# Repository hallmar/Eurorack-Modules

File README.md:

# Eurorack-Modules
Hardware: cc-by-sa-3.0

Software: CC BY-SA 4.0

All of the code in this repository is for Arduino.

But if you want to sell or do something with the software or hardware then it'd be nice to include my name and link to my Github somewhere :)

This is a general repository for any and all eurorack modules that i have designed.
I also put DIY stuff here that I made PCB's from some other designers schematic. For example the MFOS PCB.

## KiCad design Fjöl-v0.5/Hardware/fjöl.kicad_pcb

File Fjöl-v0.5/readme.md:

# Fjöl 4-Voice Midi synth, THIS IS A DEPRECATED PROJECT AND I'M ONLY KEEPING IT FOR ARCHIVING PURPOSES

Current hardware uses a high quality DAC(PCM5100) with 16bit/44.1kHz quality.

It has MIDI IN and MIDI OUT/THRU. It uses the Arturia Standard for DIN to stereo jack, so type B midi.
You can find adapters in almost every synthstore now. 

## Designed With

* KiCAD
* Arduino IDE
* Audio System Design Tool for Teensy Audio Library

## Versioning
* 1.0 - [Hardware] Original PCB
* 1.0 - [Software] Original software release
## Authors

* **Hallmar Gauti Halldórsson** 

## License
Hardware: CC BY-SA 4.0

Software: CC BY-SA 4.0

But if you want to sell or do something with the software or hardware then it'd be nice to include my name and link to my Github somewhere :)

## Acknowledgments

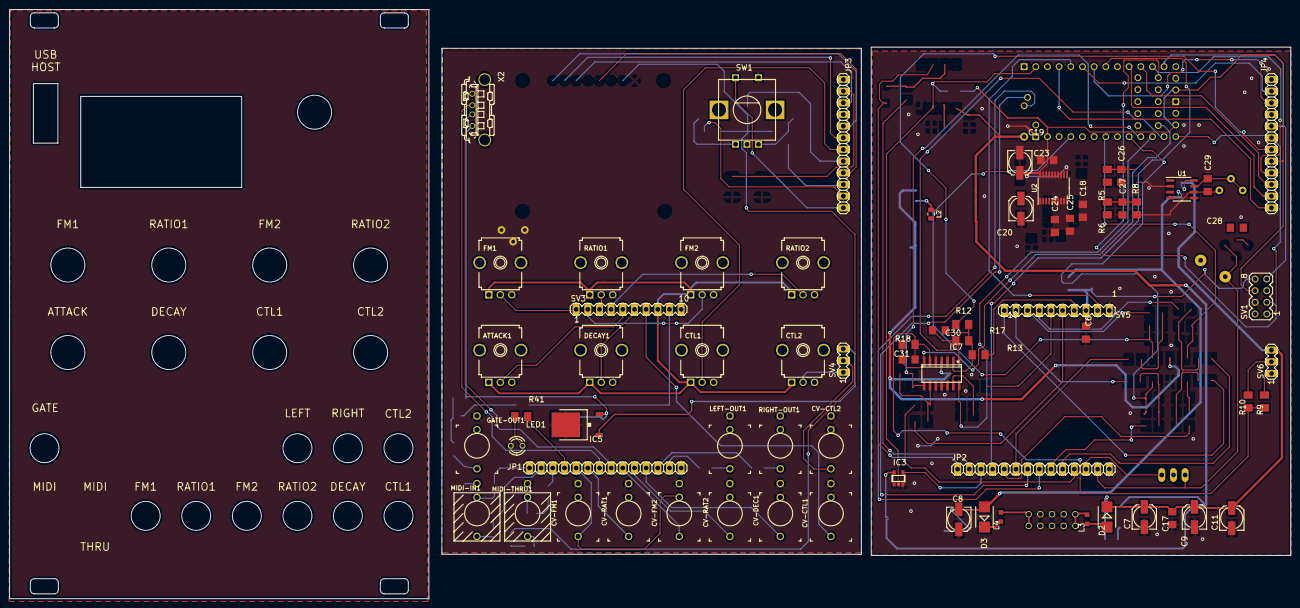
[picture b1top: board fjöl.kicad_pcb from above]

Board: 2 copper layers, 278.9 x 128.3 mm, 116 parts (0 on the bottom side), 104 nets.

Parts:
ATTACK1: 50k-lin; 9MM_SNAP-IN_POT
C1, C3, C6, C14, C15, C16, C17, C18, C23, C24, C25, C26, C27, C38, C39, C41: 100n; C1206
C2, C5, C11, C12, C13: 100µ; 153CLV-0505
C7, C8: 22u; 153CLV-0505
C9, C10, C19, C21: 10u; 153CLV-0505
C20, C22: 2.2u; 153CLV-0505
C28, C29: 100p; C1206
C30, C31: 1n; C1206
C40, C42: 10n; C1206
CTL1, CTL2: 50k lin; 9MM_SNAP-IN_POT
CV-CTL1, CV-CTL2: THONKICONNNEW; WQP-PJ301M-12_JACK
CV-DEC1: THONKICONNNEW; WQP-PJ301M-12_JACK
CV-FM1, CV-FM2: THONKICONNNEW; WQP-PJ301M-12_JACK
CV-RAT1, CV-RAT2: THONKICONNNEW; WQP-PJ301M-12_JACK
D2, D3: STPS1L30U; SMB
DECAY1: 50k-lin; 9MM_SNAP-IN_POT
FM1, FM2: 50k-lin; 9MM_SNAP-IN_POT
GAINLEFT2: 50k; BOURNS_3362P_TRIMMER
GATE-OUT1: THONKICONNNEW; WQP-PJ301M-12_JACK
IC1, IC5: 78DT; TO252
IC2: REG1117; SOT223
IC3: 741G17DBV; SOT23-5
IC4: LM4040B10; DBZ_R-PDSO-G3
IC7: TL074; SO14
JP1, JP2: PINHD-1X14; 1X14
JP3, JP4: PINHD-1X12; 1X12
L1: 33u; L_1206_3216Metric
L2: WE-CBF_0603; L_0805_2012Metric
L3, L4, L5: BLM21PG221SN1D; L2012C
L6, L7, L8, L9: BLM21AG102SN1D; L2012C
L-OUT1: 2,54_1,0
LED1: LED3MM
LEFT-OUT1: THONKICONNNEW; WQP-PJ301M-12_JACK
MIDI-IN1: THONKI-STEREO; WQP-PJ366ST_JACK
MIDI-THRU1: THONKI-STEREO; WQP-PJ366ST_JACK
R4, R36, R37, R40, R41, R43: 1k; M1206
R5, R6: 2.2K; M1206
R8: 10K; M1206
R9, R12: 200k; M1206
R10, R13: 100k; M1206
R17, R18: 66.5k; M1206
R32: 33; M1206
R33: 10; M1206
R34, R35, R38, R39, R42: 10k; M1206
RATIO1, RATIO2: 50k-lin; 9MM_SNAP-IN_POT
RIGHT-OUT1: THONKICONNNEW; WQP-PJ301M-12_JACK
SV1: MA04-2
SV2, SV4, SV6: MA03-1
SV3, SV5: MA10-1
SW1: EC12E_SW; ALPS_EC12E_SW
T1: BC847; SOT23
TP1: 2,54_1,0
U1: TL072; SO-8_3.9x4.9mm_P1.27mm
U2: PCM5100; TSSOP-20_4.4x6.5mm_P0.65mm
U$1: TEENSY40
U$2: OLED-1.3; OLED-1.3_-164-32
X1: 2510-; PAK100_2500-10
X2: KUSBVX

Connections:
5V_USB: C13.+, C16.1, IC5.2, R42.1, X2.1
+3.3V: C18.2, C19.+, JP4.8, SV1.6, U2.1, U2.10, U2.11, U2.20, U$1.3V3-1, U$1.3V3-2, U$1.ON/OFF
+3.3VA: C1.1, C2.+, C21.+, C24.2, C25.2, C38.1, C39.1, IC2.2, IC7.4, U2.8
+3.3V_F: JP3.8, L5.2
+3.3V_F1: L5.1, R32.1, R35.2, R38.2
+5V: C3.1, C5.+, IC1.2, IC3.5, U$1.VIN
+12V: C7.+, C9.+, C11.+, C14.1, C17.1, D2.C, L1.2, L2.2, SV6.3, U1.8
+12V-F: IC5.1, SV4.3
-10V: C6.1, IC4.2, R4.2, SV1.8, SV5.3
-10V_F: ATTACK1.1, CTL1.1, CTL2.1, DECAY1.1, FM1.1, FM2.1, RATIO1.1, RATIO2.1, SV3.8
-12V: C8.-, C10.-, C12.-, C15.2, D3.A, R4.1, U1.4
ATT-POT-F: ATTACK1.2, SV3.5
CONTROL1: C30.2, IC7.1, R17.2, U$1.14-A0/TX3/S-PFI_OUT
CONTROL2: C31.2, R18.2, U$1.24-A10/TX6/SCL2
CS: JP4.9, U$1.10-CS/MQSR
CS_ADC: SV1.3, U$1.32-OUTB1
CTL1-POT: JP4.7, R12.1
CTL1-POT-F: CTL1.2, JP3.7
CTL2-POT: R9.1, SV6.1
CTL2-POT-F: CTL2.2, SV4.1
CV-CTL1: R13.1, SV5.4
CV-CTL1-F: CV-CTL1.P$1_TIP, SV3.7
CV-CTL2: R10.1, SV6.2
CV-CTL2-F: CV-CTL2.P$1_TIP, SV4.2
CV-DEC-F: CV-DEC1.P$1_TIP, JP1.11
CV-FM1-F: CV-FM1.P$1_TIP, JP1.5
CV-FM2-F: CV-FM2.P$1_TIP, JP1.9
CV-RAT1-F: CV-RAT1.P$1_TIP, JP1.6
CV-RAT2-F: CV-RAT2.P$1_TIP, JP1.10
D+: JP2.7, U$1.D+
D+_F: JP1.7, X2.3
D-: JP2.8, U$1.D-
D-_F: JP1.8, X2.2
DC: JP4.3, U$1.5-IN2
DEC-POT-F: DECAY1.2, SV3.6
ENC-A: JP4.11, U$1.8-TX2/IN1
ENC-A-F: JP3.11, R34.2
ENC-B: JP4.10, U$1.9-OUT1C
ENC-B-F: JP3.10, R39.1
ENC-SW: JP4.12, U$1.2-OUT2
ENC-SW-F: JP3.12, SW1.D
FM1: IC7.14, U$1.18-A4/SDA0
FM1-POT-F: FM1.2, SV3.1
FM2: IC7.8, U$1.17-A3/TX4/SDA1
FM2-POT-F: FM2.2, SV3.2
GATE: SV5.2, U$1.3-LRCLK2
GATE-F: R40.1, SV3.9
GATE-LED: JP2.4, U$1.6-OUT1D
GATE-LED-F: JP1.4, R41.1
GND: ATTACK1.3, C13.-, C16.2, C40.1, C41.1, C42.1, CTL1.3, CTL2.3, CV-CTL1.P$2_SWITCH, CV-CTL1.P$3_SLEEVE, CV-CTL2.P$2_SWITCH, CV-CTL2.P$3_SLEEVE, CV-DEC1.P$2_SWITCH, CV-DEC1.P$3_SLEEVE, CV-FM1.P$2_SWITCH, CV-FM1.P$3_SLEEVE, CV-FM2.P$2_SWITCH, CV-FM2.P$3_SLEEVE, CV-RAT1.P$2_SWITCH, CV-RAT1.P$3_SLEEVE, CV-RAT2.P$2_SWITCH, CV-RAT2.P$3_SLEEVE, DECAY1.3, FM1.3, FM2.3, GATE-OUT1.P$3_SLEEVE, IC5.3, JP1.14, JP3.1, LED1.K, LEFT-OUT1.P$3_SLEEVE, MIDI-THRU1.P$3_SLEEVE, RATIO1.3, RATIO2.3, RIGHT-OUT1.P$3_SLEEVE, SV3.10, SW1.C, SW1.E, T1.2, X2.4, X2.M1, X2.M2
GND1: C1.2, C2.-, C3.2, C5.-, C6.2, C7.-, C8.+, C9.-, C10.+, C11.-, C12.+, C14.2, C15.1, C17.2, C18.1, C19.-, C20.-, C21.-, C23.1, C24.1, C25.1, C26.1, C27.1, C38.2, C39.2, IC1.3, IC2.1, IC3.3, IC4.1, IC7.3, IC7.5, IC7.10, IC7.11, IC7.12, JP2.14, JP4.1, SV1.4, SV2.2, SV5.1, U1.3, U1.5, U2.3, U2.9, U2.16, U2.17, U2.19, U$1.GND1, U$1.GND2, U$1.GND3, X1.3, X1.4, X1.5, X1.6, X1.7, X1.8
LEFT-OUT: C28.2, JP2.13, SV2.1, TP1.1, U1.1, U$2.1, U$2.2
LEFT-OUT-F: JP1.13, R36.1
LRCLK: U2.15, U$1.20-A6/TX5/LRCLK1
MCLK: U2.13, U$1.23-A9/CRX1/CCLK1
MIDI-IN-L-F: JP1.2, L6.1
MIDI-IN-R-F: JP1.1, L7.1
MIDI-RX: IC3.2, U$1.0-RX1
MIDI-THRU-R-F: JP1.3, R33.1
MIDI-TX: IC3.4, JP2.3
MISO: SV1.5, U$1.12-MIO/MQSL
MOSI: JP4.5, SV1.7, U$1.11-MOSI/CTX1
unnamed: C20.+, U2.5
unnamed: C22.+, U2.2
unnamed: C22.-, U2.4
unnamed: C23.2, U2.18
unnamed: C26.2, R5.1
unnamed: C27.2, R6.1, R8.2
unnamed: C28.1, U1.2, U$2.3
unnamed: C29.1, GAINLEFT2.3, R8.1, U1.6
unnamed: C30.1, IC7.2, R12.2, R13.2, R17.1
unnamed: C31.1, R9.2, R10.2, R18.1
unnamed: C40.2, R34.1, R35.1, SW1.A
unnamed: C41.2, MIDI-IN1.P$3_SLEEVE
unnamed: C42.2, R38.1, R39.2, SW1.B
unnamed: D2.A, L3.2
unnamed: D3.C, L4.2
unnamed: GATE-OUT1.P$1_TIP, R43.2
unnamed: IC1.1, L1.1
unnamed: IC2.3, L2.1
unnamed: L3.1, X1.9, X1.10
unnamed: L4.1, X1.1, X1.2
unnamed: L6.2, MIDI-IN1.P$1_TIP
unnamed: L7.2, MIDI-IN1.P$2_SWITCH
unnamed: L8.1, R32.2
unnamed: L8.2, MIDI-THRU1.P$1_TIP
unnamed: L9.1, R33.2
unnamed: L9.2, MIDI-THRU1.P$2_SWITCH
unnamed: LED1.A, R41.2
unnamed: LEFT-OUT1.P$1_TIP, R36.2
unnamed: R37.2, RIGHT-OUT1.P$1_TIP
unnamed: R40.2, T1.1
unnamed: R42.2, R43.1, T1.3
RAT1-POT-F: RATIO1.2, SV3.3
RAT2-POT-F: RATIO2.2, SV3.4
RATIO1: IC7.7, U$1.22-A8/CTX1
RIGHT-OUT: C29.2, GAINLEFT2.1, GAINLEFT2.2, JP2.12, L-OUT1.1, SV2.3, U1.7
RIGHT-OUT-F: JP1.12, R37.1
SCK: JP4.6, SV1.1, U$1.13-SCK/CRX1/LED
SCLK: U2.12, U$1.21-A7/RX5/BCLK1
SDATA: U2.14, U$1.7-RX2/OUT1A
SWITCH: JP4.2, U$1.4-BCLK2
dac_left: R5.2, U2.6
dac_right: R6.2, U2.7

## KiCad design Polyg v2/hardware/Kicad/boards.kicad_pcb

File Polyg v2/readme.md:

# Polyg v2 8-Voice Midi synth

This new version has a dedicated MIDI thru instead of routing it into the Teensy and back out. 
And it has alot of improvements of the hardware.

[Youtube demo](https://www.youtube.com/watch?v=QhJZFhLLbBc&feature=youtu.be)

[Mouser cart](https://www.mouser.com/ProjectManager/ProjectDetail.aspx?AccessID=3288d77cba)

8 Voice polyphonic synthesizer with selectable Karplus strong(8 voice plucky string synth) or a 8 voice FM synth with square,sine,triangle and sawtooth. It has a basic FM(techincally Phase Modulation, like the DX7) with one Modulator. 
There's an index knob to set the ratio, decay for the operator and the amount of FM applied.

Current hardware uses a high quality 16bit/44.1kHz DAC(CD4334).

It has MIDI IN and MIDI OUT/THRU. It uses the Arturia Standard for DIN to stereo jack, so type B midi.
You can find adapters in almost every synthstore now. 

## Where/how to order
I won't have any PCB's in stock any time soon. This project is pretty much abandoned.
You have my approval of making your own, just remember to credit me.

## Designed With

* Eagle CAD
* Arduino IDE
* Audio System Design Tool for Teensy Audio Library

## Versioning
* 1.0 - [Hardware] Original PCB batch with wrong silkscreen
* 1.1 - [Hardware] v1 of PCBs
* 1.0 - [Software] Original software release
* 2.0 - [Hardware] v2 of PCB is made with improvements
* 2.0 - [Hardware] v2 of firmware is written
## Authors

* **Hallmar Gauti Halldórsson** 

## License
Hardware: cc-by-sa-3.0

Software: MIT license

But if you want to sell or do something with the software or hardware then it'd be nice to include my name and link to my Github somewhere :)

## Acknowledgments
Alot of the inspiration for this project came from the [String Theory](https://makesynthsnotwar.com/modules/stringtheory/) eurorack module by Make Synths Not War.
The original String Theory was programmed by [Jan Ostman](https://janostman.wordpress.com).

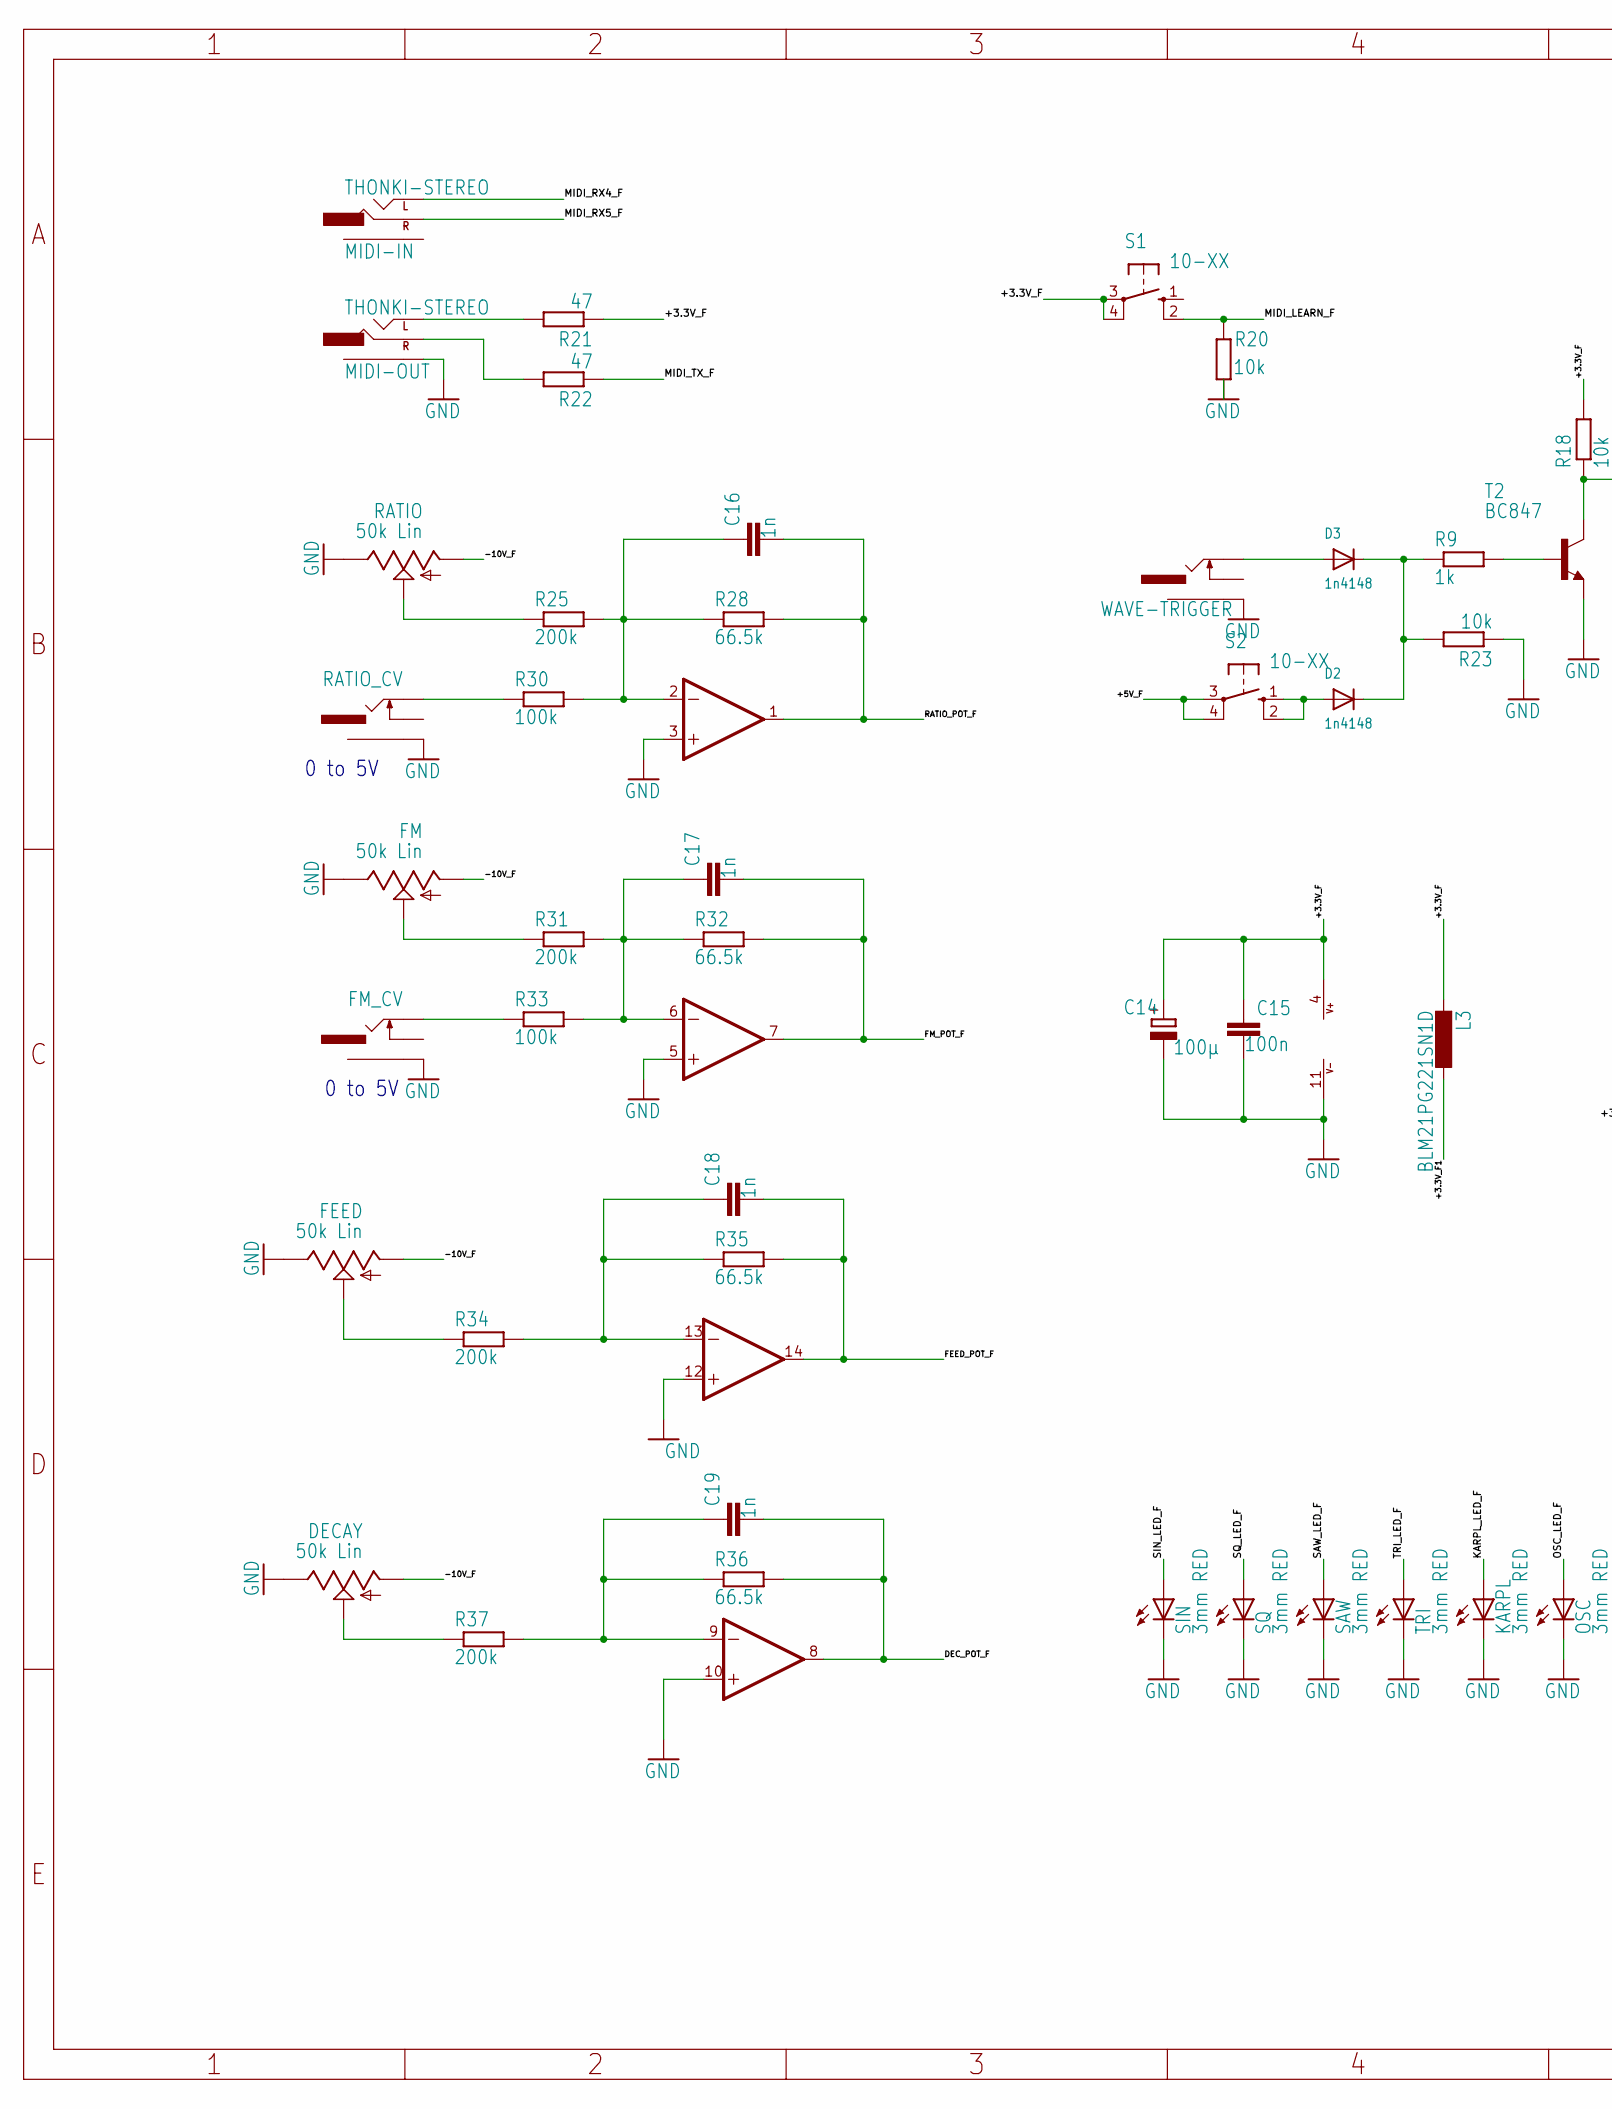
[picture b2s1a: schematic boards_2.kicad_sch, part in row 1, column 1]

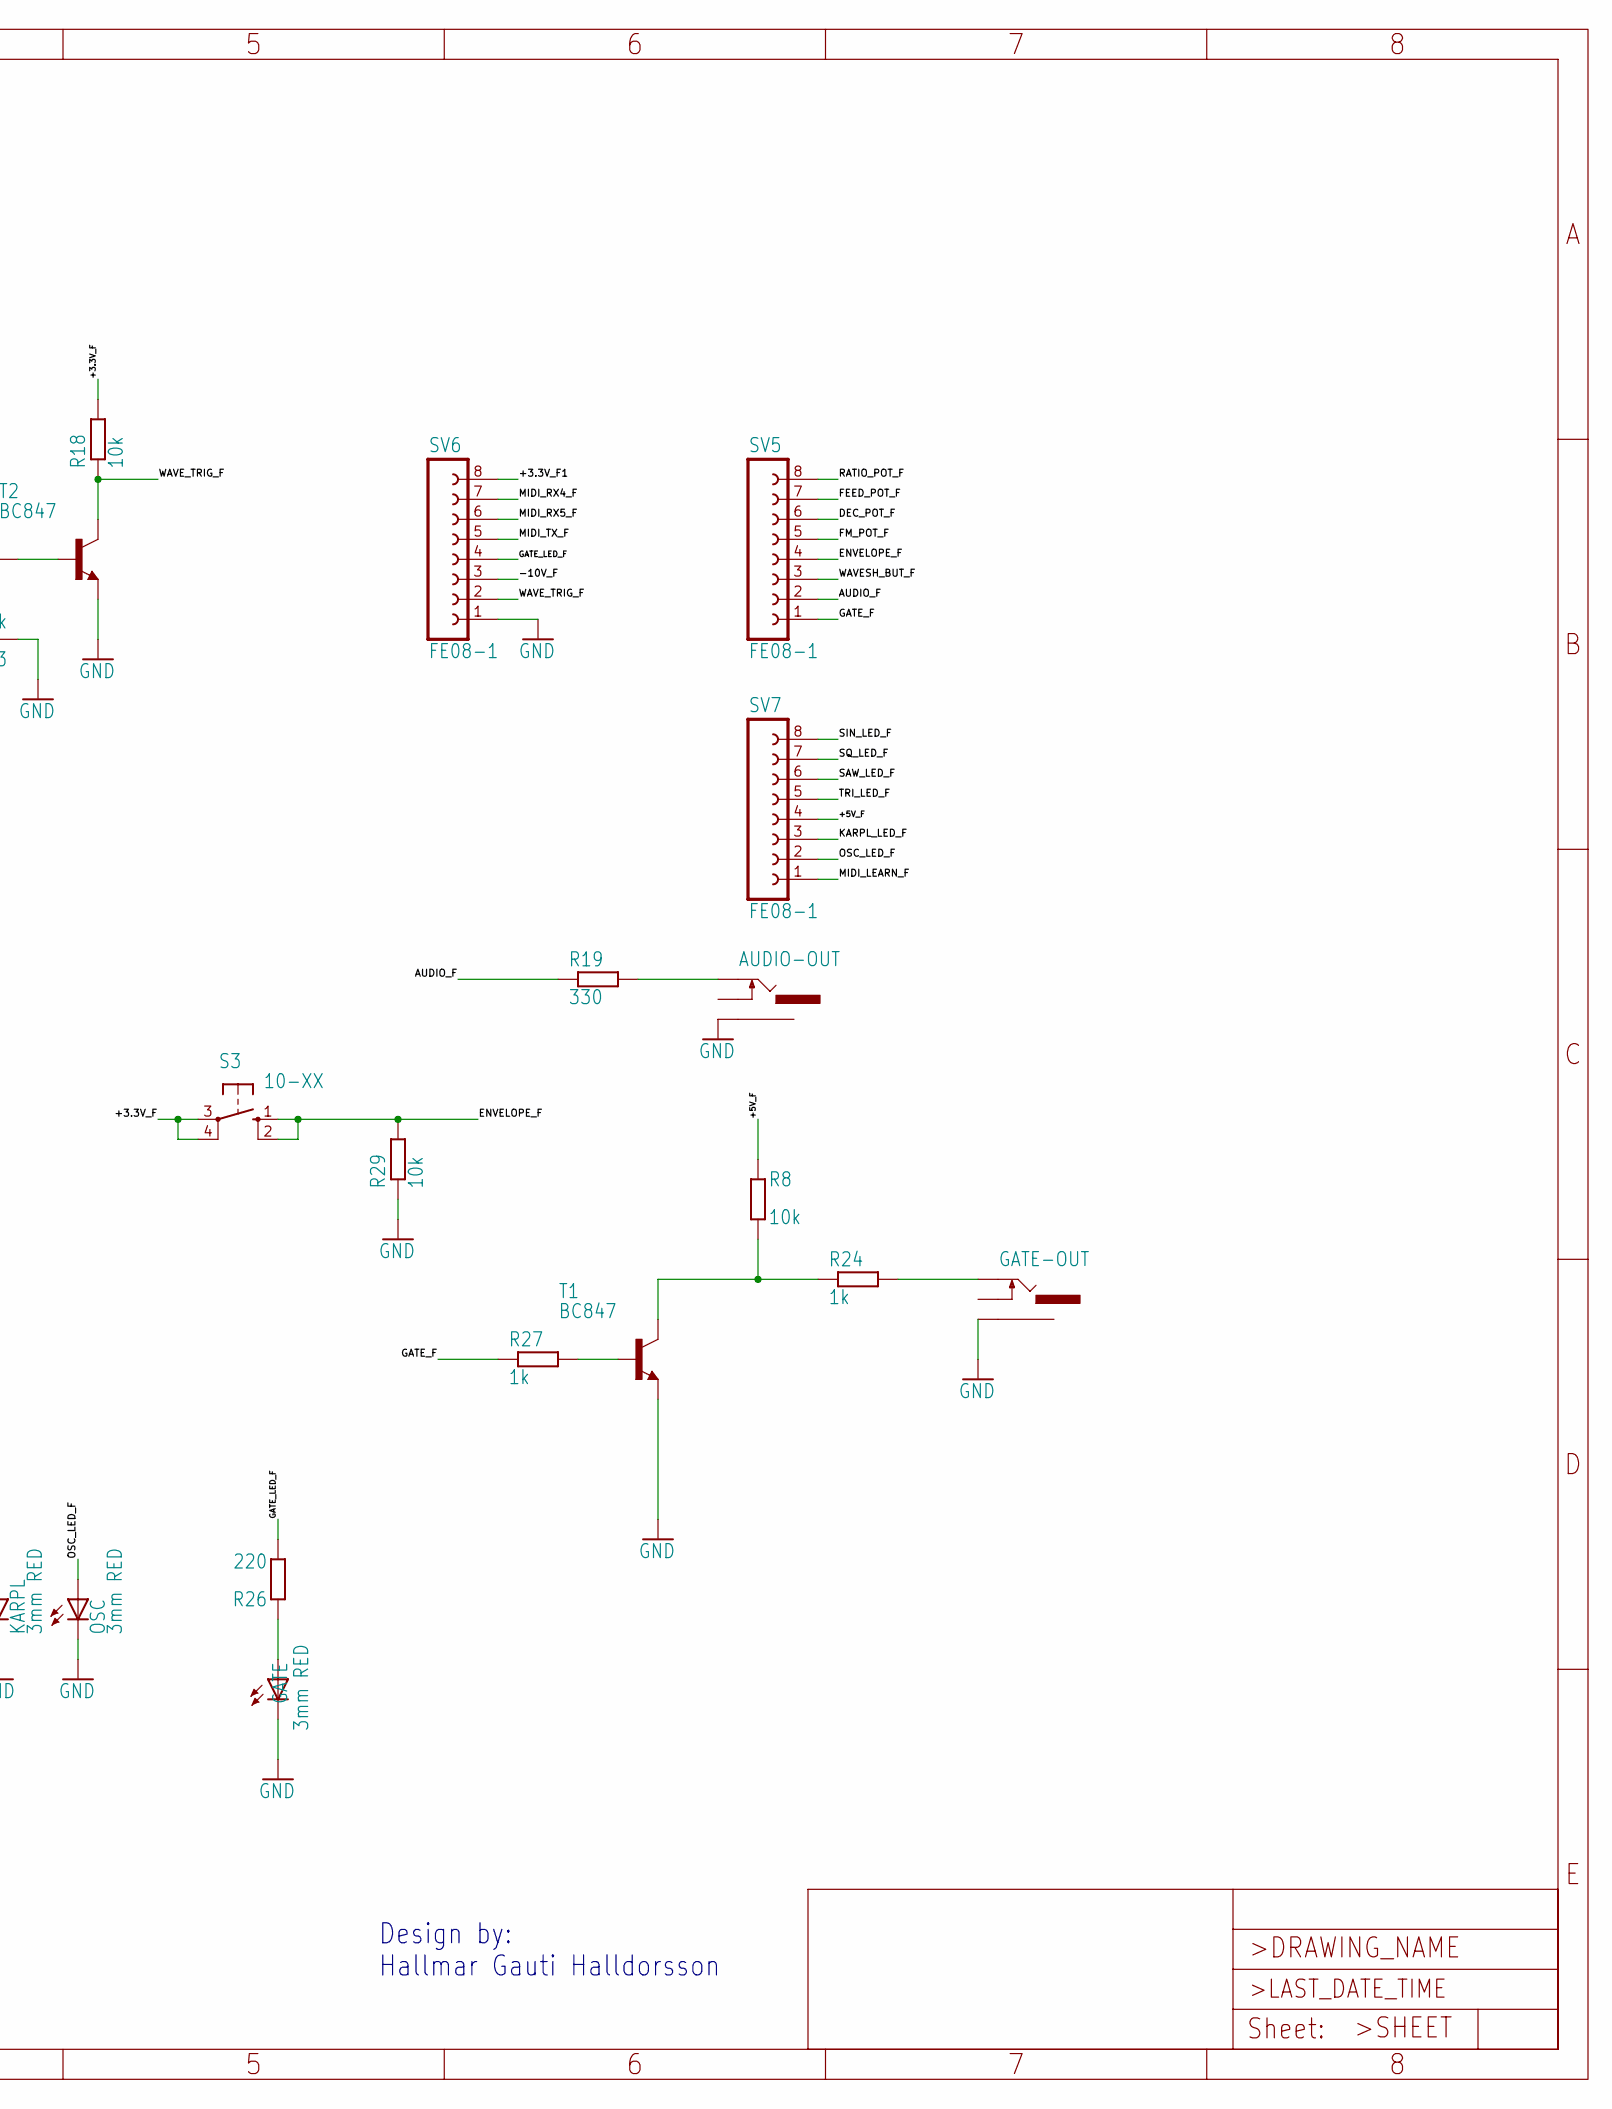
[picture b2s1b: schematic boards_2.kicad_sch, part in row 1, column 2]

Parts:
AUDIO-OUT: THONKICONNNEW; WQP-PJ301M-12_JACK
C14: 100µ; 153CLV-0505
C15: 100n; C1206
C16, C17, C18, C19: 1n; C1206
D2, D3: 1n4148; SOD-123
DECAY: 50k Lin; 9MM_SNAP-IN_POT
FEED: 50k Lin; 9MM_SNAP-IN_POT
FM: 50k Lin; 9MM_SNAP-IN_POT
FM_CV: THONKICONNNEW; WQP-PJ301M-12_JACK
GATE: 3mm RED; LED3MM
GATE-OUT: THONKICONNNEW; WQP-PJ301M-12_JACK
KARPL: 3mm RED; LED3MM
L3: BLM21PG221SN1D; L2012C
MIDI-IN: THONKI-STEREO; WQP-PJ366ST_JACK
MIDI-OUT: THONKI-STEREO; WQP-PJ366ST_JACK
OSC: 3mm RED; LED3MM
R8, R18, R20, R23, R29: 10k; M1206
R9, R24, R27: 1k; M1206
R19: 330; M1206
R21, R22: 47; M1206
R25, R31, R34, R37: 200k; M1206
R26: 220; M1206
R28, R32, R35, R36: 66.5k; M1206
R30, R33: 100k; M1206
RATIO: 50k Lin; 9MM_SNAP-IN_POT
RATIO_CV: THONKICONNNEW; WQP-PJ301M-12_JACK
S1, S2, S3: 10-XX; B3F-10XX
SAW: 3mm RED; LED3MM
SIN: 3mm RED; LED3MM
SQ: 3mm RED; LED3MM
SV5, SV6, SV7: FE08-1; FE08
T1, T2: BC847; SOT23
TRI: 3mm RED; LED3MM
U1: MCP6004_SMD; SO14
WAVE-TRIGGER: THONKICONNNEW; WQP-PJ301M-12_JACK

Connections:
+3.3V_F: C14.+, C15.1, L3.2, R18.2, R21.1, S1.3, S1.4 (P1), S3.3, S3.4 (P1), U1.4 (V+)
+3.3V_F1: L3.1, SV6.8
+5V_F: R8.1, S2.3, S2.4 (P1), SV7.4
-10V_F: DECAY.1 (A), FEED.1 (A), FM.1 (A), RATIO.1 (A), SV6.3
AUDIO_F: R19.1, SV5.2
B: R27.2, T1.1 (B)
DEC_POT_F: C19.2, R36.2, SV5.6, U1.8 (OUT)
ENVELOPE_F: R29.2, S3.1 (S), S3.2 (S1), SV5.4
FEED_POT_F: C18.2, R35.2, SV5.7, U1.14 (OUT)
FM_POT_F: C17.2, R32.2, SV5.5, U1.7 (OUT)
GATE_F: R27.1, SV5.1
GATE_LED_F: R26.2, SV6.4
GND: AUDIO-OUT.P$3_SLEEVE (SLEEVE), C14.-, C15.2, DECAY.3 (E), FEED.3 (E), FM.3 (E), FM_CV.P$3_SLEEVE (SLEEVE), GATE.K (C), GATE-OUT.P$3_SLEEVE (SLEEVE), KARPL.K (C), MIDI-OUT.P$3_SLEEVE (SLEEVE), OSC.K (C), R20.2, R23.1, R29.1, RATIO.3 (E), RATIO_CV.P$3_SLEEVE (SLEEVE), SAW.K (C), SIN.K (C), SQ.K (C), SV6.1, T1.2 (E), T2.2 (E), TRI.K (C), U1.3 (+IN), U1.5 (+IN), U1.10 (+IN), U1.11 (V-), U1.12 (+IN), WAVE-TRIGGER.P$3_SLEEVE (SLEEVE)
KARPL_LED_F: KARPL.A, SV7.3
MIDI_LEARN_F: R20.1, S1.2 (S1), SV7.1
MIDI_RX4_F: MIDI-IN.P$1_TIP (LEFT), SV6.7
MIDI_RX5_F: MIDI-IN.P$2_SWITCH (RIGHT), SV6.6
MIDI_TX_F: R22.1, SV6.5
unnamed: AUDIO-OUT.P$1_TIP (TIP), R19.2
unnamed: GATE.A, R26.1
unnamed: MIDI-OUT.P$2_SWITCH (RIGHT), R22.2
unnamed: MIDI-OUT.P$1_TIP (LEFT), R21.2
unnamed: R8.2, R24.1, T1.3 (C)
unnamed: R9.2, T2.1 (B)
unnamed: D2.A, S2.1 (S), S2.2 (S1)
unnamed: D3.A, WAVE-TRIGGER.P$1_TIP (TIP)
unnamed: D2.C, D3.C, R9.1, R23.2
unnamed: GATE-OUT.P$1_TIP (TIP), R24.2
unnamed: R25.1, RATIO.2 (S)
unnamed: C16.1, R25.2, R28.1, R30.2, U1.2 (-IN)
unnamed: R30.1, RATIO_CV.P$1_TIP (TIP)
unnamed: FM.2 (S), R31.1
unnamed: C17.1, R31.2, R32.1, R33.2, U1.6 (-IN)
unnamed: FM_CV.P$1_TIP (TIP), R33.1
unnamed: FEED.2 (S), R34.1
unnamed: DECAY.2 (S), R37.1
unnamed: C19.1, R36.1, R37.2, U1.9 (-IN)
unnamed: C18.1, R34.2, R35.1, U1.13 (-IN)
OSC_LED_F: OSC.A, SV7.2
RATIO_POT_F: C16.2, R28.2, SV5.8, U1.1 (OUT)
SAW_LED_F: SAW.A, SV7.6
SIN_LED_F: SIN.A, SV7.8
SQ_LED_F: SQ.A, SV7.7
TRI_LED_F: SV7.5, TRI.A
WAVESH_BUT_F: SV5.3
WAVE_TRIG_F: R18.1, SV6.2, T2.3 (C)

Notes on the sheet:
Design by: Hallmar Gauti Halldorsson
0 to 5V

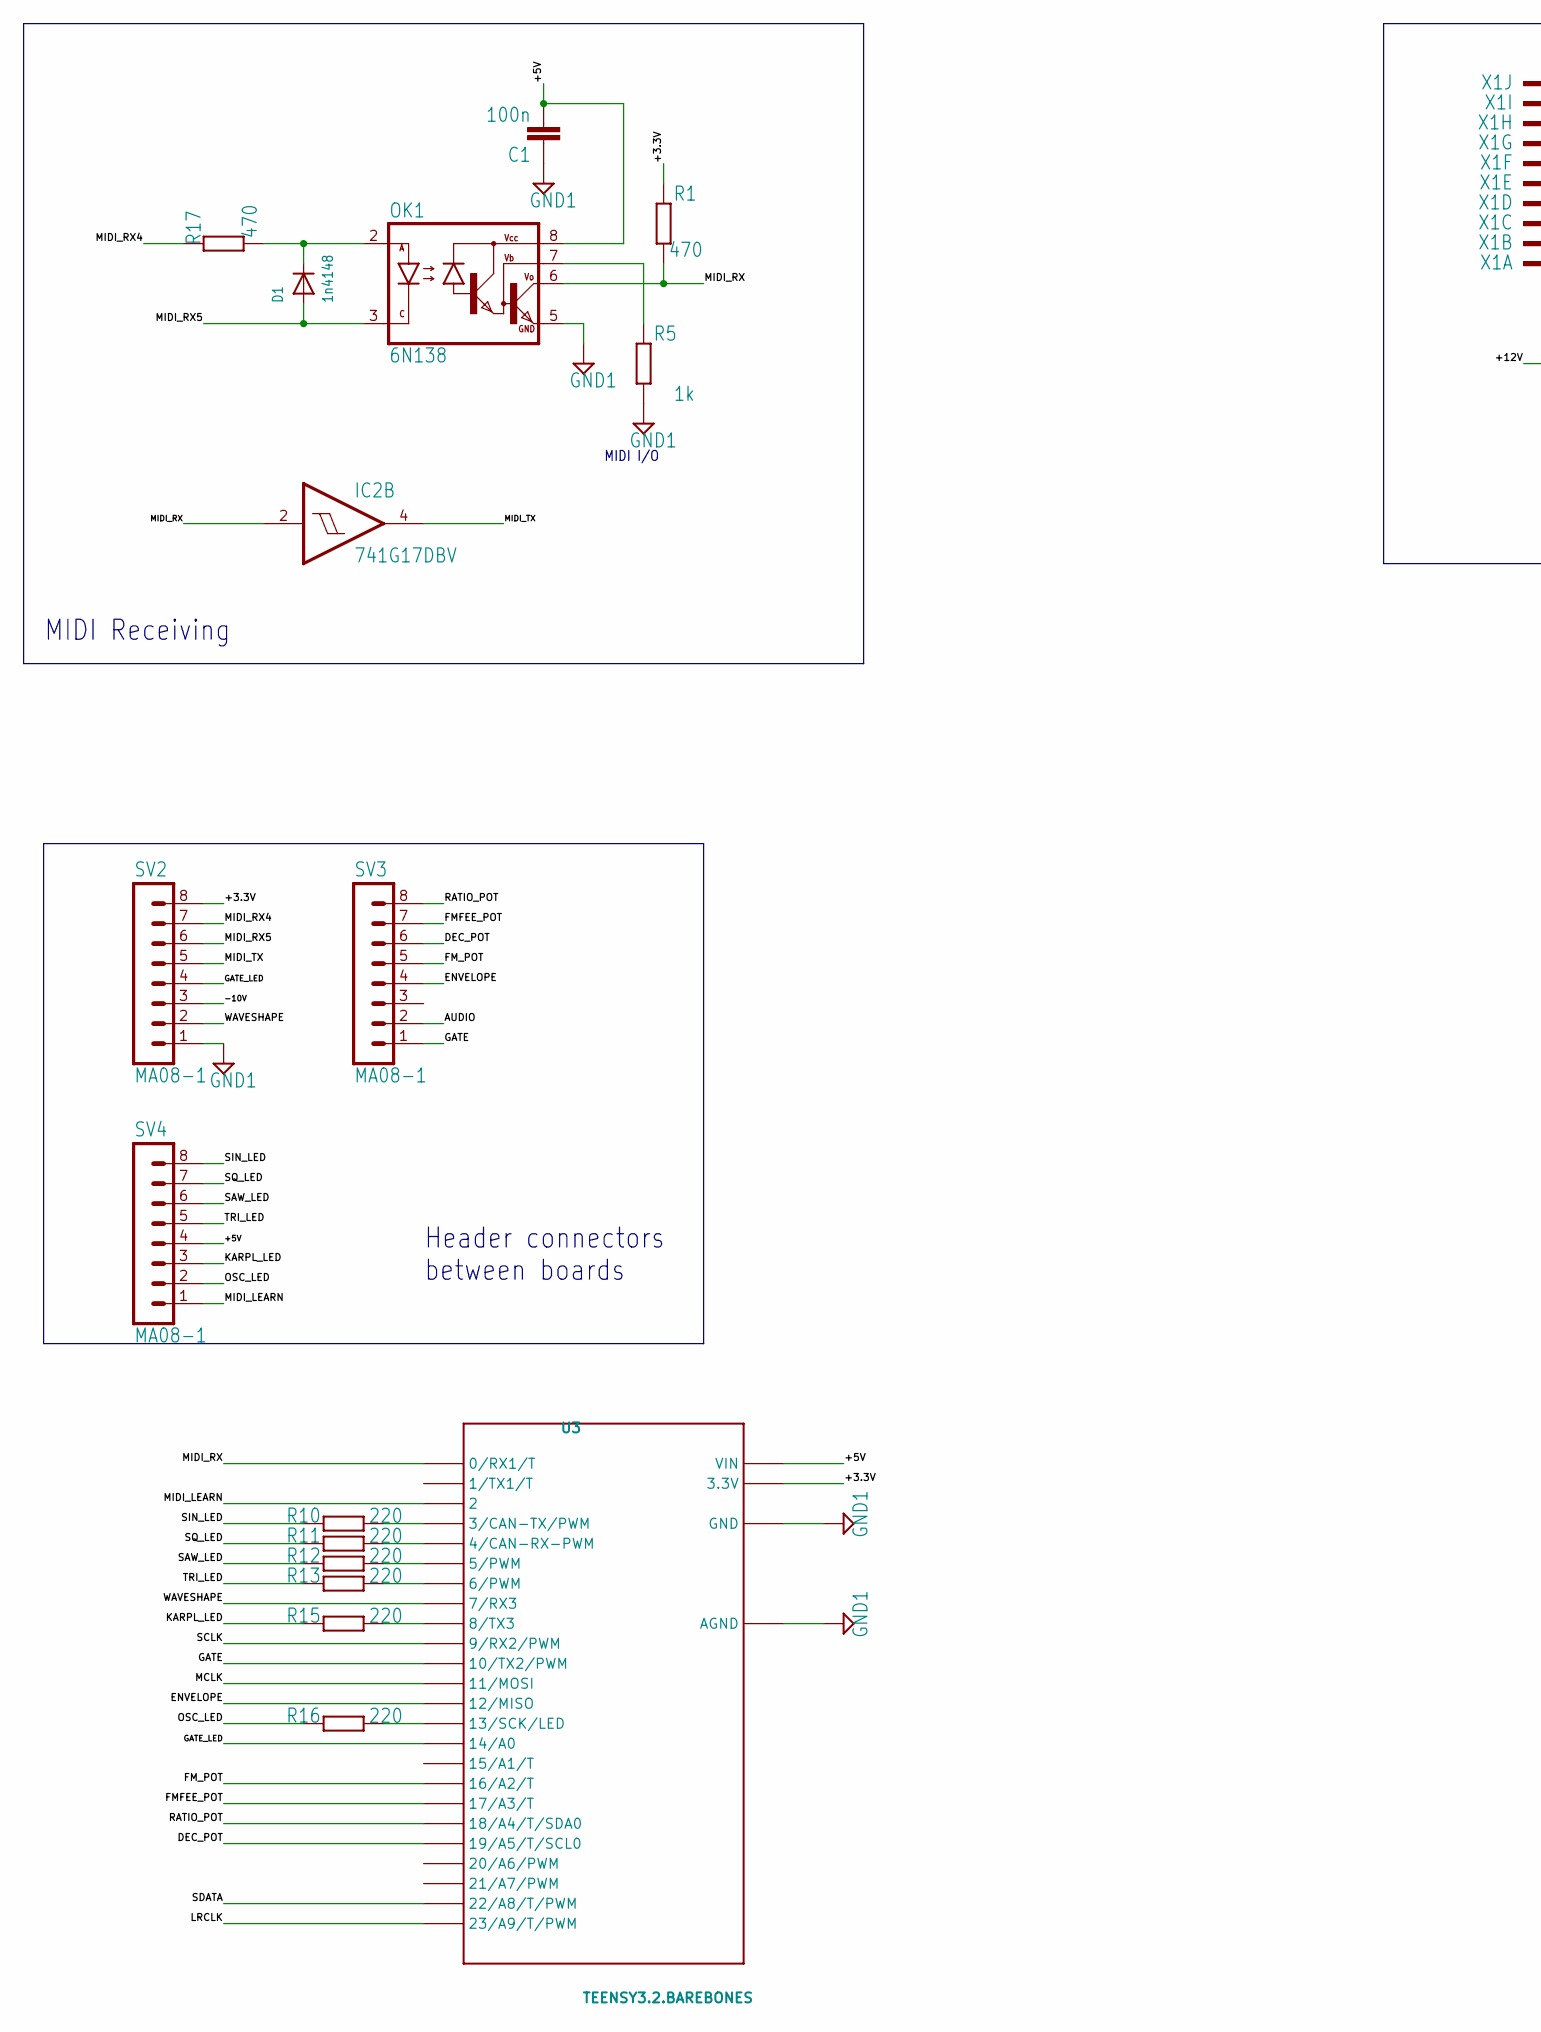
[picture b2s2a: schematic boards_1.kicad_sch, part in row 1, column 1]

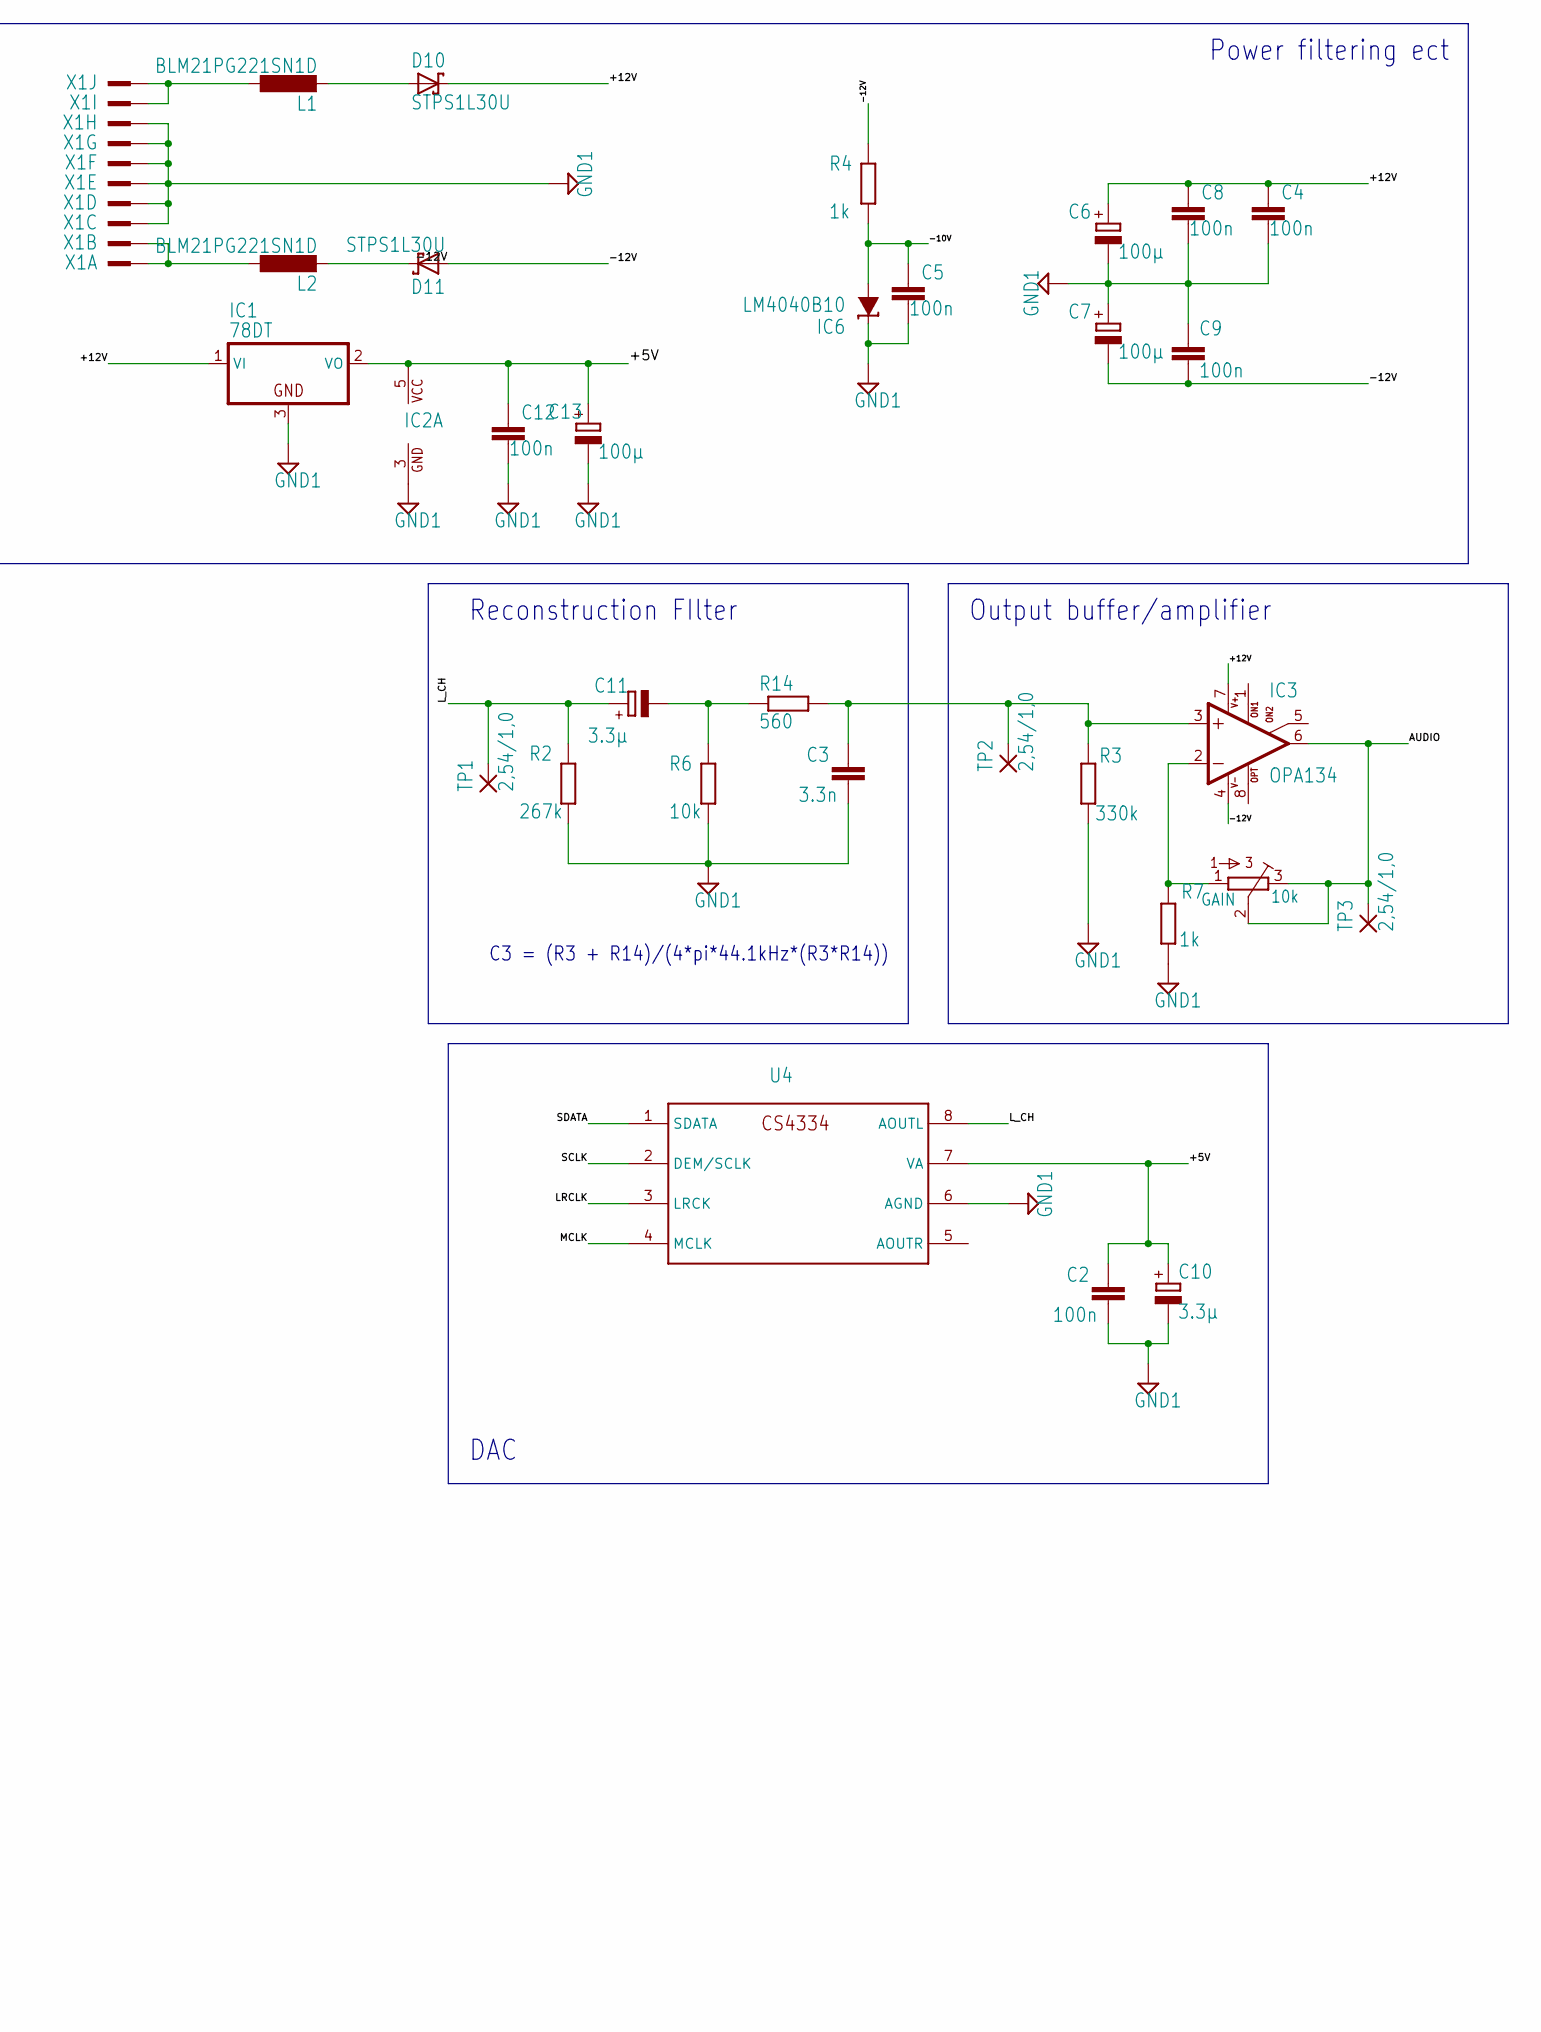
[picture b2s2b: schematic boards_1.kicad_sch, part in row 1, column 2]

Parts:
C1, C2, C4, C5, C8, C9, C12: 100n; C1206
C3: 3.3n; C1206
C6, C7, C13: 100µ; 153CLV-0505
C10, C11: 3.3µ; 153CLV-0405
D1: 1n4148; SOD-123
D10, D11: STPS1L30U; SMB
GAIN: 10k; BOURNS_3362P_TRIMMER
IC1: 78DT; TO252
IC2: 741G17DBV; SOT23-5
IC3: OPA134; SO08
IC6: LM4040B10; DBZ_R-PDSO-G3
L1, L2: BLM21PG221SN1D; L2012C
OK1: 6N138; DIL08
R1, R17: 470; M1206
R2: 267k; M1206
R3: 330k; M1206
R4, R5, R7: 1k; M1206
R6: 10k; M1206
R10, R11, R12, R13, R15, R16: 220; M1206
R14: 560; M1206
SV2, SV3, SV4: MA08-1
TP1, TP2, TP3: 2,54/1,0; 2,54_1,0
U3: TEENSY3.2.BAREBONES; TEENSY3.2_BAREBONES
U4: CS4334; SOIC127P600X175-8N
X1: 2510-; PAK100_2500-10

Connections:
+3.3V: R1.2, SV2.8, U3.3.3V
+5V: C1.2, C2.1, C10.+, C12.1, C13.+, IC1.2 (VO), IC2.5 (VCC), OK1.8 (VCC), SV4.4, U3.VIN, U4.7 (VA)
+12V: C4.1, C6.+, C8.1, D10.C, IC1.1 (VI), IC3.7 (V+)
-10V: C5.1, IC6.2 (A), R4.2, SV2.3
-12V: C7.-, C9.2, D11.A, IC3.4 (V-), R4.1
AUDIO: GAIN.2, GAIN.3, IC3.6 (OUT), SV3.2, TP3.1
DEC_POT: SV3.6, U3.19/A5 (19/A5/T/SCL0)
ENVELOPE: SV3.4, U3.12 (12/MISO)
FMFEE_POT: SV3.7, U3.17/A3 (17/A3/T)
FM_POT: SV3.5, U3.16/A2 (16/A2/T)
GATE: SV3.1, U3.10 (10/TX2/PWM)
GATE_LED: SV2.4, U3.14/A0
GND1: C1.1, C2.2, C3.2, C4.2, C5.2, C6.-, C7.+, C8.2, C9.1, C10.-, C12.2, C13.-, IC1.3 (GND), IC2.3 (GND), IC6.1 (C), OK1.5 (GND), R2.2, R3.2, R5.1, R6.2, R7.2, SV2.1, U3.AGND, U3.GND, U4.6 (AGND), X1.3, X1.4, X1.5, X1.6, X1.7, X1.8
KARPL_LED: R15.2, SV4.3
LRCLK: U3.23/A9 (23/A9/T/PWM), U4.3 (LRCK)
L_CH: C11.+, R2.1, TP1.1, U4.8 (AOUTL)
MCLK: U3.11 (11/MOSI), U4.4 (MCLK)
MIDI_LEARN: SV4.1, U3.2
MIDI_RX: IC2.2 (I), OK1.6 (VO), R1.1, U3.0 (0/RX1/T)
MIDI_RX4: R17.2, SV2.7
MIDI_RX5: D1.A, OK1.3 (C), SV2.6
MIDI_TX: IC2.4 (O), SV2.5
unnamed: C11.-, R6.1, R14.1
unnamed: D1.C, OK1.2 (A), R17.1
unnamed: OK1.7 (VB), R5.2
unnamed: GAIN.1, IC3.2 (-IN), R7.1
unnamed: R16.1, U3.13 (13/SCK/LED)
unnamed: C3.1, IC3.3 (+IN), R3.1, R14.2, TP2.1
unnamed: R10.1, U3.3 (3/CAN-TX/PWM)
unnamed: R11.1, U3.4 (4/CAN-RX-PWM)
unnamed: R12.1, U3.5 (5/PWM)
unnamed: R13.1, U3.6 (6/PWM)
unnamed: R15.1, U3.8 (8/TX3)
unnamed: L1.1, X1.9, X1.10
unnamed: L2.1, X1.1, X1.2
unnamed: D10.A, L1.2
unnamed: D11.C, L2.2
OSC_LED: R16.2, SV4.2
RATIO_POT: SV3.8, U3.18/A4 (18/A4/T/SDA0)
SAW_LED: R12.2, SV4.6
SCLK: U3.9 (9/RX2/PWM), U4.2 (DEM/SCLK)
SDATA: U3.22/A8 (22/A8/T/PWM), U4.1 (SDATA)
SIN_LED: R10.2, SV4.8
SQ_LED: R11.2, SV4.7
TRI_LED: R13.2, SV4.5
WAVESHAPE: SV2.2, U3.7 (7/RX3)

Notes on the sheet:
Reconstruction FIlter
MIDI I/O
Output buffer/amplifier
DAC
Header connectors between boards
C3 = (R3 + R14)/(4*pi*44.1kHz*(R3*R14))
MIDI Receiving
Power filtering ect
